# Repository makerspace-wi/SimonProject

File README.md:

# Simon Project

ESP32-basierte Steuerung fuer Fallblattanzeigen (MAN/Krone/Vossloh) mit:
- WiFi Access Point
- Weboberflaeche/HTTP-API
- Serieller Ausgabe im Krone-Protokoll
- I2C-Transfer von Byte-Werten an 3 Slave-Adressen (ADTrans)

## Projektziel

Dieses Projekt stellt mit einem ESP32 einen lokalen Access Point bereit. Ueber HTTP-Endpoints koennen Anzeigeinhalte gesetzt oder geloescht werden. Die Ausgabe an die Fallblattmodule erfolgt seriell im Format:

- Startbyte: `0x88`
- Adresse: `adress`
- Wert: `flip`
- Endbyte: `0x81`

## Verwendete Plattform

- MCU/Board: ESP32 (`wemos_d1_uno32`)
- Framework: Arduino
- Build-System: PlatformIO
- Webserver: `ESP32WebServer`
- mDNS: `ESPmDNS`
- I2C: `Wire`

Konfiguration: [platformio.ini](platformio.ini)

## Build und Upload

### Build

```bash
~/.platformio/penv/bin/platformio run
```

### Upload (Beispiel)

```bash
~/.platformio/penv/bin/platformio run -t upload
```

## Netzwerkverhalten

Beim Start erzeugt der ESP32 einen Access Point:
- SSID: `fallblatt.local`
- Passwort: `Fallblattanzeige`

Zusatz: mDNS wird mit Hostname `fallblatt` initialisiert.

## HTTP-Endpoints

Implementierung in [src/main.cpp](src/main.cpp).

### 1) Startseite

- `GET /`
- Liefert die HTML-Oberflaeche aus `MAIN_page` (Datei [src/web.h](src/web.h)).

### 2) Anzeige loeschen

- `GET /clear`
- Loescht/neutralisiert alle angesteuerten Fallblattpositionen.

### 3) Anzeige setzen

- `GET /flip`
- Erwartete Query-Parameter:
  - `b` = Betreiber
  - `g` = Gattung
  - `n` = Zugnummer
  - `s` = Abfahrtsstunde
  - `m` = Abfahrtsminute
  - `i1` = Info 1
  - `i2` = Info 2
  - `d` = Zwischenziel
  - `z` = Ziel

Beispiel:

```text
/flip?b=1&g=2&n=42&s=12&m=34&i1=5&i2=6&d=7&z=8
```

Hinweis:
- Der Endpoint `/flip` steuert zusaetzlich 3 I2C-Module (ADTrans) ueber `I2C_ADDR_1..3`.
- Je nach Laenge der Zugnummer werden Ziffern auf UART-Fallblattmodule und I2C-Module verteilt.

### 4) Zweites Modul (direkt im Programm gesteuert)

Die zweite serielle Schnittstelle (19200 Baud, BREAK-Protokoll) wird ohne eigenen HTTP-Endpoint direkt im Programmablauf gesteuert.

Aktuell erfolgt die Ansteuerung am Ende von `/flip` mit:

- Zieladresse aus `MODULE2_DIRECT_ADDR`
- Position aus dem bereits berechneten Feld `ziel`

Damit geht die Kommunikation fuer das zweite Modul nicht separat ueber den Webserver.

## I2C-Konfiguration

Standardwerte in [platformio.ini](platformio.ini):

- `I2C_ADDR_1=0x38`
- `I2C_ADDR_2=0x39`
- `I2C_ADDR_3=0x3A`

Optionale Pinbelegung (auskommentiert):
- `I2C_SDA_PIN`
- `I2C_SCL_PIN`

Wenn beide Pins gesetzt sind, wird `Wire.begin(SDA, SCL)` verwendet.
Andernfalls nutzt das Projekt `Wire.begin()` mit Board-Default.

## Genutzte IO-Pins

Aktueller Stand gemaess [platformio.ini](platformio.ini) und [src/main.cpp](src/main.cpp):

- Debug-UART (`Serial`): ueber USB-Seriell (Monitor 115200 Baud).
- Signal-UART (`Serial2`, 4800 Baud, 8E2):
  - TX: GPIO17 (`UART_SIGNAL_TX_PIN`)
  - RX: GPIO16 (`UART_SIGNAL_RX_PIN`)
- Modul-2-UART (`Serial1`, 19200 Baud, 8N1, BREAK-faehig):
  - TX: GPIO26 (`UART_MODULE2_TX_PIN`)
  - RX: GPIO27 (`UART_MODULE2_RX_PIN`)
  - Optional RS485 Driver-Enable: `UART_MODULE2_RS485_DE_PIN` (Standard `-1` = aus)
- I2C (`Wire`):
  - Aktuell keine festen Pins im Build-Flag gesetzt.
  - Es werden daher die Board-Defaults verwendet (`Wire.begin()`).
  - Optional konfigurierbar ueber `I2C_SDA_PIN` und `I2C_SCL_PIN` in [platformio.ini](platformio.ini).

Hinweis:
- Auf vielen ESP32-Boards liegt USB-Debug intern auf UART0 (typisch TX0=GPIO1, RX0=GPIO3).
- Fuer die Fallblattansteuerung wird ausschliesslich `Serial2` genutzt.
- Die ADTrans-I2C-Module werden mit `sendByte(...)` angesteuert (kein separater HTTP-I2C-Endpoint).

## Fallblatt-Adressen (seriell)

Die adressierten Module sind in [src/main.cpp](src/main.cpp) festgelegt, u. a.:
- Logo: `0x05`
- Gattung: `0x04`
- Zeichen 1/2: `0x03`, `0x02`
- Stunde/Minute: `0x01`, `0x00`
- Info 1/2: `0x07`, `0x06`
- Zwischenziel/Ziel: `0x08`, `0x09`

## Troubleshooting

### Build-Task in VS Code schlaegt fehl, Terminal-Build funktioniert

Symptom:
- VS-Code-Task meldet Fehler, manueller Build ist erfolgreich.

Pruefung/Fix:
- Sicherstellen, dass [/.vscode/tasks.json](.vscode/tasks.json) den PlatformIO-Pfad aus dem Python-Environment nutzt.
- Build direkt testen:

```bash
~/.platformio/penv/bin/platformio run
```

### Include-Fehler / IntelliSense findet Header nicht

Symptom:
- Meldung wie "Aktualisieren Sie Ihren includePath".

Pruefung/Fix:
- Einmal erfolgreichen Build ausfuehren, damit PlatformIO die Projektmetadaten aktualisiert.
- VS Code neu laden, falls die Meldung bestehen bleibt.
- In [platformio.ini](platformio.ini) das richtige Environment pruefen (`ESP32_WROOM`).

### Upload funktioniert nicht

Symptom:
- `run -t upload` bricht mit Port- oder Verbindungsfehler ab.

Pruefung/Fix:
- USB-Kabel/Port wechseln.
- Board-Typ in [platformio.ini](platformio.ini) pruefen (`wemos_d1_uno32`).
- Upload separat testen:

```bash
~/.platformio/penv/bin/platformio run -t upload
```

### I2C-Geraet reagiert nicht

Symptom:
- Ziffern auf den ADTrans-Modulen fehlen oder bleiben auf Leerwert.

Pruefung/Fix:
- I2C-Adressen in [platformio.ini](platformio.ini) mit den Slave-Adressen abgleichen (`I2C_ADDR_1..3`).
- Falls eigene Pins noetig sind, `I2C_SDA_PIN` und `I2C_SCL_PIN` in [platformio.ini](platformio.ini) aktivieren.
- GND zwischen ESP32 und I2C-Slaves gemeinsam verbinden.

### mDNS/Hostname nicht erreichbar

Symptom:
- `fallblatt.local` wird nicht aufgeloest.

Pruefung/Fix:
- Direkt per IP aufrufen statt Hostname.
- Sicherstellen, dass das Endgeraet im Access-Point des ESP32 eingebucht ist.
- AP-Daten pruefen: SSID `fallblatt.local`, Passwort `Fallblattanzeige`.

## Hinweise

- Das Projekt ist fuer die aktuelle ESP32-PlatformIO-Umgebung ausgelegt.
- Bei Problemen zuerst Build lokal pruefen und die Werte in [platformio.ini](platformio.ini) kontrollieren.

1. OMEGA-Modul über RS485 ansteuern
Das OMEGA-Modul hängt an Serial1 (RS485, Pins 26/27, 19200 Baud, 8N1). Du hast bereits die Funktion module2SetPosition(), die den Befehl 0xC0 (Set Position) sendet. Diese kannst du für das OMEGA-Modul verwenden – aber mit der richtigen Adresse deines OMEGA-Moduls.

Statt:

cpp
setflip(logoadress, betreiber);
schreibst du:

cpp
// Betreiber an OMEGA-Modul über RS485 senden
// MODULE2_DIRECT_ADDR muss die tatsächliche Adresse des OMEGA-Moduls sein
module2SetPosition(static_cast<uint8_t>(MODULE2_DIRECT_ADDR), static_cast<uint8_t>(betreiber & 0xFF));

Super einfach, wir machen es Schritt für Schritt.
Das Tool ist ein kleines Programm, das über die serielle RS485-Schnittstelle Befehle an Module mit Adresse 0 bis 255 sendet.

Siehe auch: README.md

Was das Tool macht

Es sendet immer ein Telegramm im Format: BREAK + FF + COMMAND + ADDR + optionale Daten.

Du gibst an:
Port, Command, und Zieladresse(n).

Zieladressen können sein:
eine Adresse, ein Bereich oder alle 0..255.

Einmalige Einrichtung

Terminal im Projekt öffnen und in den Ordner wechseln:
cd "/Users/dieter/Documents/PlatformIO/Projects/Simon Project/omega-rs485-tool"

Virtuelle Umgebung anlegen:
python3 -m venv .venv

Aktivieren:
source .venv/bin/activate

Abhängigkeit installieren:
pip install -r requirements.txt

Erster Test ohne Senden

Damit siehst du nur, was gesendet würde:
python omega_rs485_tool.py --port /dev/cu.usbserial-0001 --cmd C8 --addr 29 --dry-run

Wenn das gut aussieht: --dry-run entfernen.

Einfaches echtes Senden

TEST-Command C8 an Adresse 29:
python omega_rs485_tool.py --port /dev/cu.usbserial-0001 --cmd C8 --addr 29

An alle Adressen 0..255:
python omega_rs485_tool.py --port /dev/cu.usbserial-0001 --cmd C8 --all

Beispiel mit Antwort lesen

Firmware-Version lesen, erwartet 2 Antwort-Bytes:
python omega_rs485_tool.py --port /dev/cu.usbserial-0001 --cmd D4 --all --read-bytes 2 --delay-ms 5

Ausgabe zeigt dann pro Adresse TX und ggf. RX.

Häufige Stolpersteine

Falscher Port: dann kommt meist sofort ein Öffnungsfehler.

Falsche Baudrate: hier ist 19200 Standard.

RS485-Richtung/Adapter: bei manchen Adaptern muss DE/RE korrekt geschaltet sein.

Erst immer mit einer Adresse testen, dann Bereich oder all.

Wenn du willst, gehen wir jetzt zusammen live durch deinen ersten echten Lauf, und ich sage dir genau, welchen Befehl du als Nächstes eingibst.

Top, dann ist hier Kommando 2 (Full-Scan 0..255 mit TEST-Befehl C8):

~/.platformio/penv/bin/python omega_rs485_tool.py --port /dev/cu.usbserial-0001 --cmd C8 --all --delay-ms 5

Optional erst als Trockenlauf:

~/.platformio/penv/bin/python omega_rs485_tool.py --port /dev/cu.usbserial-0001 --cmd C8 --all --delay-ms 5 --dry-run

So gibst du den seriellen Port wieder frei:

Laufendes Python-Skript stoppen
Im Terminal, in dem das Tool läuft: Control + C
Erst dadurch wird die serielle Verbindung geschlossen.
Virtuelle Umgebung verlassen
Befehl: deactivate
Falls Port trotzdem noch blockiert ist
Prüfen, welcher Prozess den Port hält:
lsof | grep cu.usbserial
Dann den betreffenden Prozess beenden:
kill -9 PID
Kurz gesagt:

Für den Port ist vor allem Control + C wichtig.
deactivate beendet nur die venv, nicht automatisch ein laufendes Skript.

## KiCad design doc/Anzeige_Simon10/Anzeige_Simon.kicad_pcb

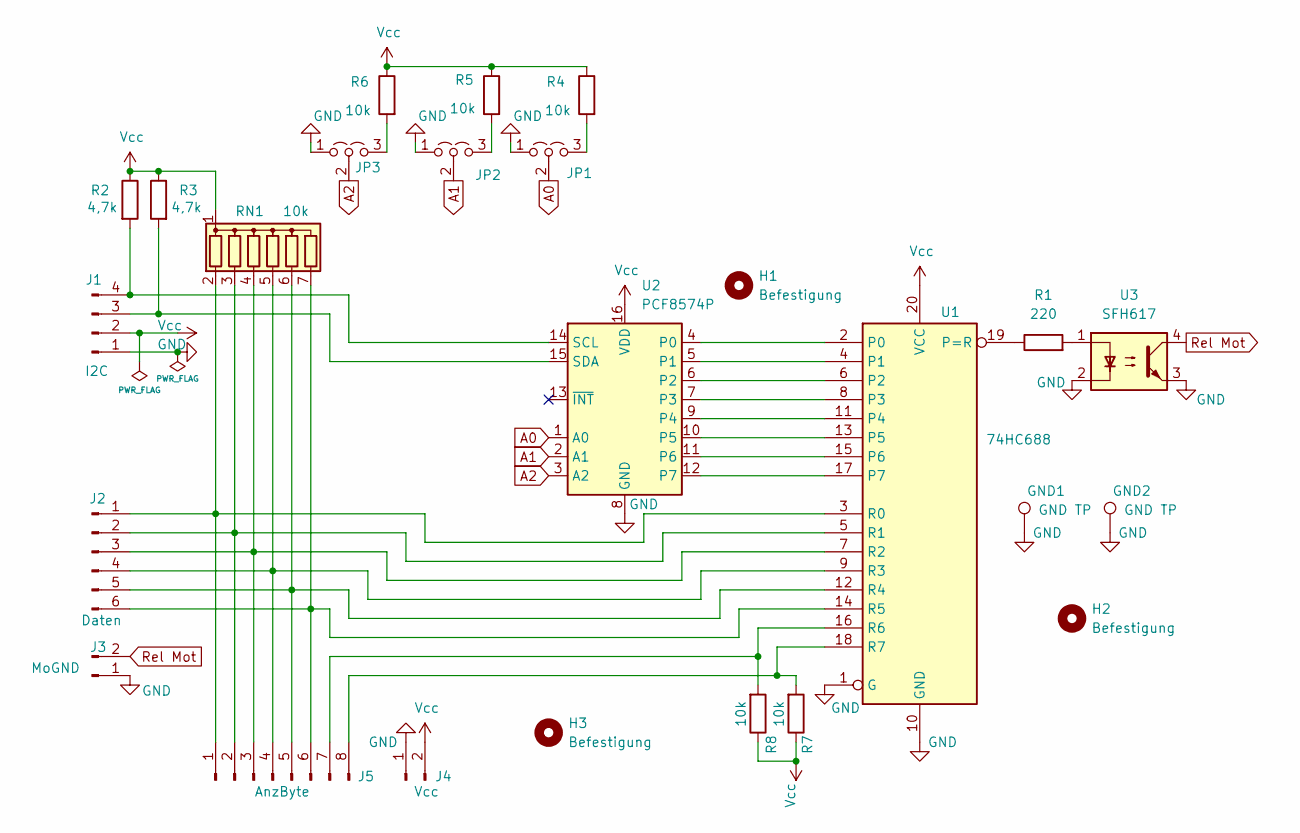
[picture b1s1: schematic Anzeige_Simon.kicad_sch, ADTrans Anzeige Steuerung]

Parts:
GND1, GND2: GND TP; SolderWirePad_1x01_SMD_1x2mm
H1, H2, H3: Befestigung; MountingHole_3.2mm_M3_ISO14580
J1: I2C; JST_XH_B4B-XH-A_1x04_P2.50mm_Vertical
J2: Daten; JST_XH_B6B-XH-A_1x06_P2.50mm_Vertical
J3: MoGND; JST_XH_B2B-XH-A_1x02_P2.50mm_Vertical
J4: Vcc; PinHeader_1x02_P2.54mm_Vertical
J5: AnzByte; PinHeader_1x08_P2.54mm_Vertical
JP1, JP2, JP3: Jumper_3_Open; SolderJumper-3_P1.3mm_Open_RoundedPad1.0x1.5mm
R1: 220; R_0805_2012Metric_Pad1.20x1.40mm_HandSolder
R2, R3: 4,7k; R_0805_2012Metric_Pad1.20x1.40mm_HandSolder
R4, R5, R6, R7, R8: 10k; R_0805_2012Metric_Pad1.20x1.40mm_HandSolder
RN1: 10k; R_Array_SIP7
U1: 74HC688; DIP-20_W7.62mm_Socket_LongPads
U2: PCF8574P; DIP-16_W7.62mm
U3: SFH617; DIP-4_W7.62mm

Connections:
A0: JP1.2 (C), U2.1 (A0)
A1: JP2.2 (C), U2.2 (A1)
A2: JP3.2 (C), U2.3 (A2)
GND: GND1.1 (1_1), GND2.1 (1_1), J1.1, J3.1, J4.1, JP1.1 (A), JP2.1 (A), JP3.1 (A), U1.1 (G), U1.10 (GND), U2.8 (GND), U3.2, U3.3
unnamed: J1.3, R3.2, U2.15 (SDA)
unnamed: J1.4, R2.2, U2.14 (SCL)
unnamed: J2.1, J5.1, RN1.2 (R1), U1.3 (R0)
unnamed: J2.2, J5.2, RN1.3 (R2), U1.5 (R1)
unnamed: J2.3, J5.3, RN1.4 (R3), U1.7 (R2)
unnamed: J2.4, J5.4, RN1.5 (R4), U1.9 (R3)
unnamed: J2.5, J5.5, RN1.6 (R5), U1.12 (R4)
unnamed: J2.6, J5.6, RN1.7 (R6), U1.14 (R5)
unnamed: J5.7, R8.2, U1.16 (R6)
unnamed: J5.8, R7.2, U1.18 (R7)
unnamed: JP1.3 (B), R4.2
unnamed: JP2.3 (B), R5.2
unnamed: JP3.3 (B), R6.2
unnamed: R1.2, U3.1
unnamed: U1.2 (P0), U2.4 (P0)
unnamed: U1.4 (P1), U2.5 (P1)
unnamed: U1.6 (P2), U2.6 (P2)
unnamed: U1.8 (P3), U2.7 (P3)
unnamed: U1.11 (P4), U2.9 (P4)
unnamed: U1.13 (P5), U2.10 (P5)
unnamed: U1.15 (P6), U2.11 (P6)
unnamed: U1.17 (P7), U2.12 (P7)
unnamed: R1.1, U1.19 (P=R)
Rel Mot: J3.2, U3.4
Vcc: J1.2, J4.2, R2.1, R3.1, R4.1, R5.1, R6.1, R7.1, R8.1, RN1.1 (common), U1.20 (VCC), U2.16 (VDD)

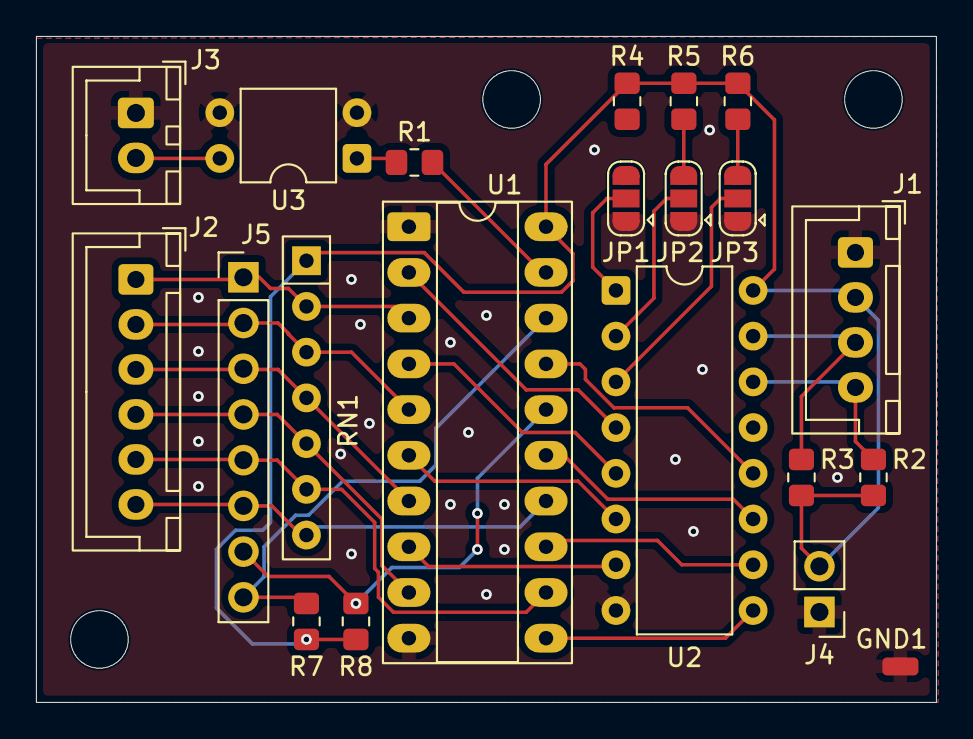
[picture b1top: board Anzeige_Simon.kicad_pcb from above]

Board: 2 copper layers, 50.0 x 37.0 mm, 25 parts (1 on the bottom side), 29 nets.
